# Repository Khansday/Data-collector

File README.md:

**THIS PROJECT IS NO LONGER UNDER DEVELOPMENT**

This aims to monitor the safety of vulnerable road users, particularly cyclists, by developing a black box system that collects and analyzes data on user conditions, environmental factors, and vehicle surroundings.
Initially using Raspberry Pi, the system evolved to a more reliable architecture featuring the **Portenta H7 microcontroller**, **Nicla Sense Me environmental sensors**, **Lidar Sensor**, and **GNSS**, all integrated with **ISD Card** to log all the data.
Recent tests showed **improved responsiveness**, faster **GNSS fixes**, and reliable data logging, although further refinements are needed to stabilize **air quality readings** and optimize **power efficiency** for extended use.

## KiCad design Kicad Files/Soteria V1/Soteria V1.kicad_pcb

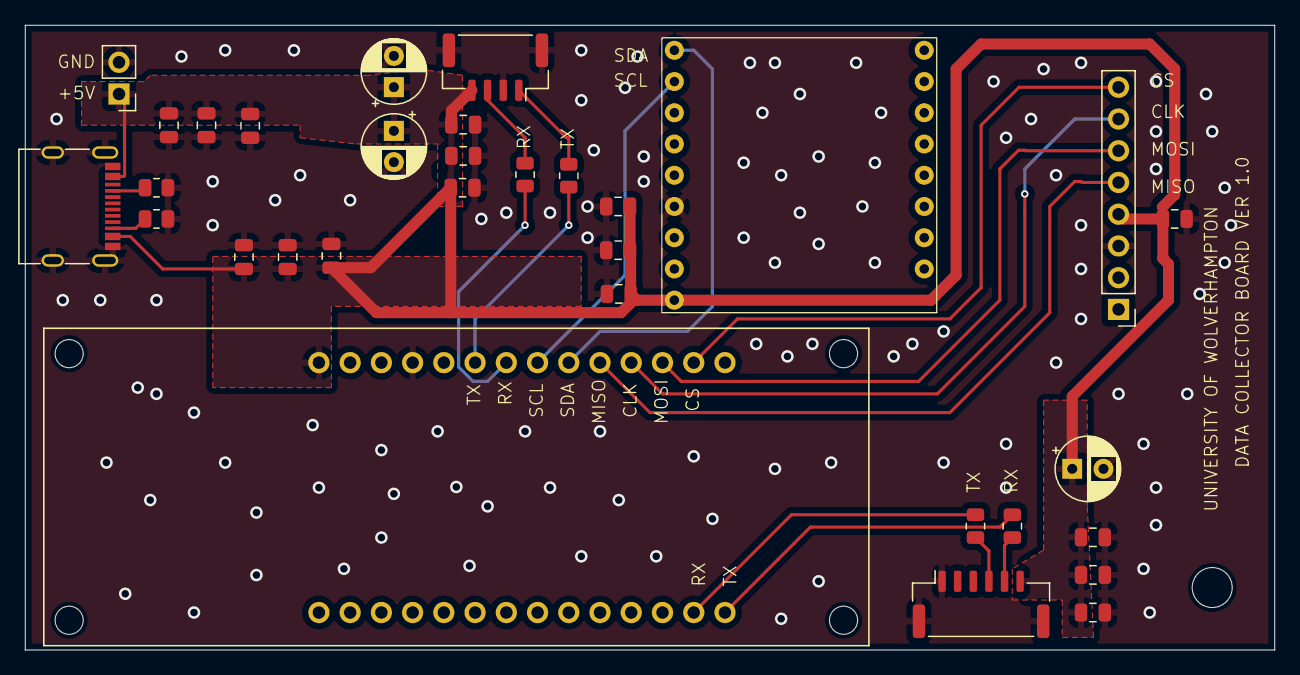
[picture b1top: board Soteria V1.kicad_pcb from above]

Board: 2 copper layers, 100.0 x 50.0 mm, 32 parts (0 on the bottom side), 18 nets.

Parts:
C1, C4, C7, C14, C18: 10u; C_0805_2012Metric
C2, C5, C8, C15, C19, C23: 1u; C_0805_2012Metric
C3, C6, C9, C16, C20: 0.1u; C_0805_2012Metric
C17, C21, C22: 470u; CP_Radial_D5.0mm_P2.50mm
J1: Conn_01x02_Pin; PinHeader_1x02_P2.54mm_Vertical
J3: Conn_01x08; PinHeader_1x08_P2.54mm_Vertical
J4: Conn_01x06_MountingPin; JST_GH_SM06B-GHS-TB_1x06-1MP_P1.25mm_Horizontal
J5: Conn_01x04_MountingPin; JST_GH_SM04B-GHS-TB_1x04-1MP_P1.25mm_Horizontal
J6: USB_C_Receptacle_USB2.0_16P; USB_C_Receptacle_G-Switch_GT-USB-7010ASV
R2, R12: 5.1K; R_0805_2012Metric
R6, R7, R8, R9: 0; R_0805_2012Metric
U1: Portenta_H7
U2: Nicla

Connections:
+5V: C1.1, C2.1, C3.1, C4.1, C5.1, C6.1, C7.1, C8.1, C9.1, C14.1, C15.1, C16.1, C17.1, C18.1, C19.1, C20.1, C21.1, C22.1, C23.1, J1.1, J3.4, J4.6, J5.4, J6.A4 (VBUS), J6.A9 (VBUS), J6.B4 (VBUS), J6.B9 (VBUS), U1.15 (+5V), U2.9 (VIN)
/I2C SCL: U1.22 (D12_I2C_SCL), U2.2 (SCL)
/I2C SDA: U1.23 (D11_I2C_SDA), U2.1 (SDA)
/SD CLK: J3.7, U1.25 (D9_SPI_CLK)
/SD CS: J3.8, U1.27 (D7_SP_CS)
/SD MISO: J3.5, U1.24 (D10_SPI_MISO)
/SD MOSI: J3.6, U1.26 (D8_SPI_MOSI)
/UART1 RX: R7.1, U1.21 (D13_UART1_RX)
/UART1 TX: R6.1, U1.20 (D14_UART1_TX)
/UART6 RX: R9.1, U1.13 (D4_UART6_RX)
/UART6 TX: R8.1, U1.14 (D5_UART6_TX)
GND: C1.2, C2.2, C3.2, C4.2, C5.2, C6.2, C7.2, C8.2, C9.2, C14.2, C15.2, C16.2, C17.2, C18.2, C19.2, C20.2, C21.2, C22.2, C23.2, J1.2, J3.3, J4.1, J4.MP (MountPin), J5.2, J5.MP (MountPin), J6.A1 (GND), J6.A12 (GND), J6.B1 (GND), J6.B12 (GND), J6.S1 (SHIELD), R2.2, R12.2, U1.18 (GND), U2.6 (GND)
unnamed: J4.4, R9.2
unnamed: J4.5, R8.2
unnamed: J5.1, R6.2
unnamed: J5.3, R7.2
unnamed: J6.A5 (CC1), R2.1
unnamed: J6.B5 (CC2), R12.1

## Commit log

2024-12-31 Modularised code
2024-12-31 Rmoved old code file
2025-03-07 added all other codes for other parts of the system. Added the Kicad files
2025-03-07 Added reports
